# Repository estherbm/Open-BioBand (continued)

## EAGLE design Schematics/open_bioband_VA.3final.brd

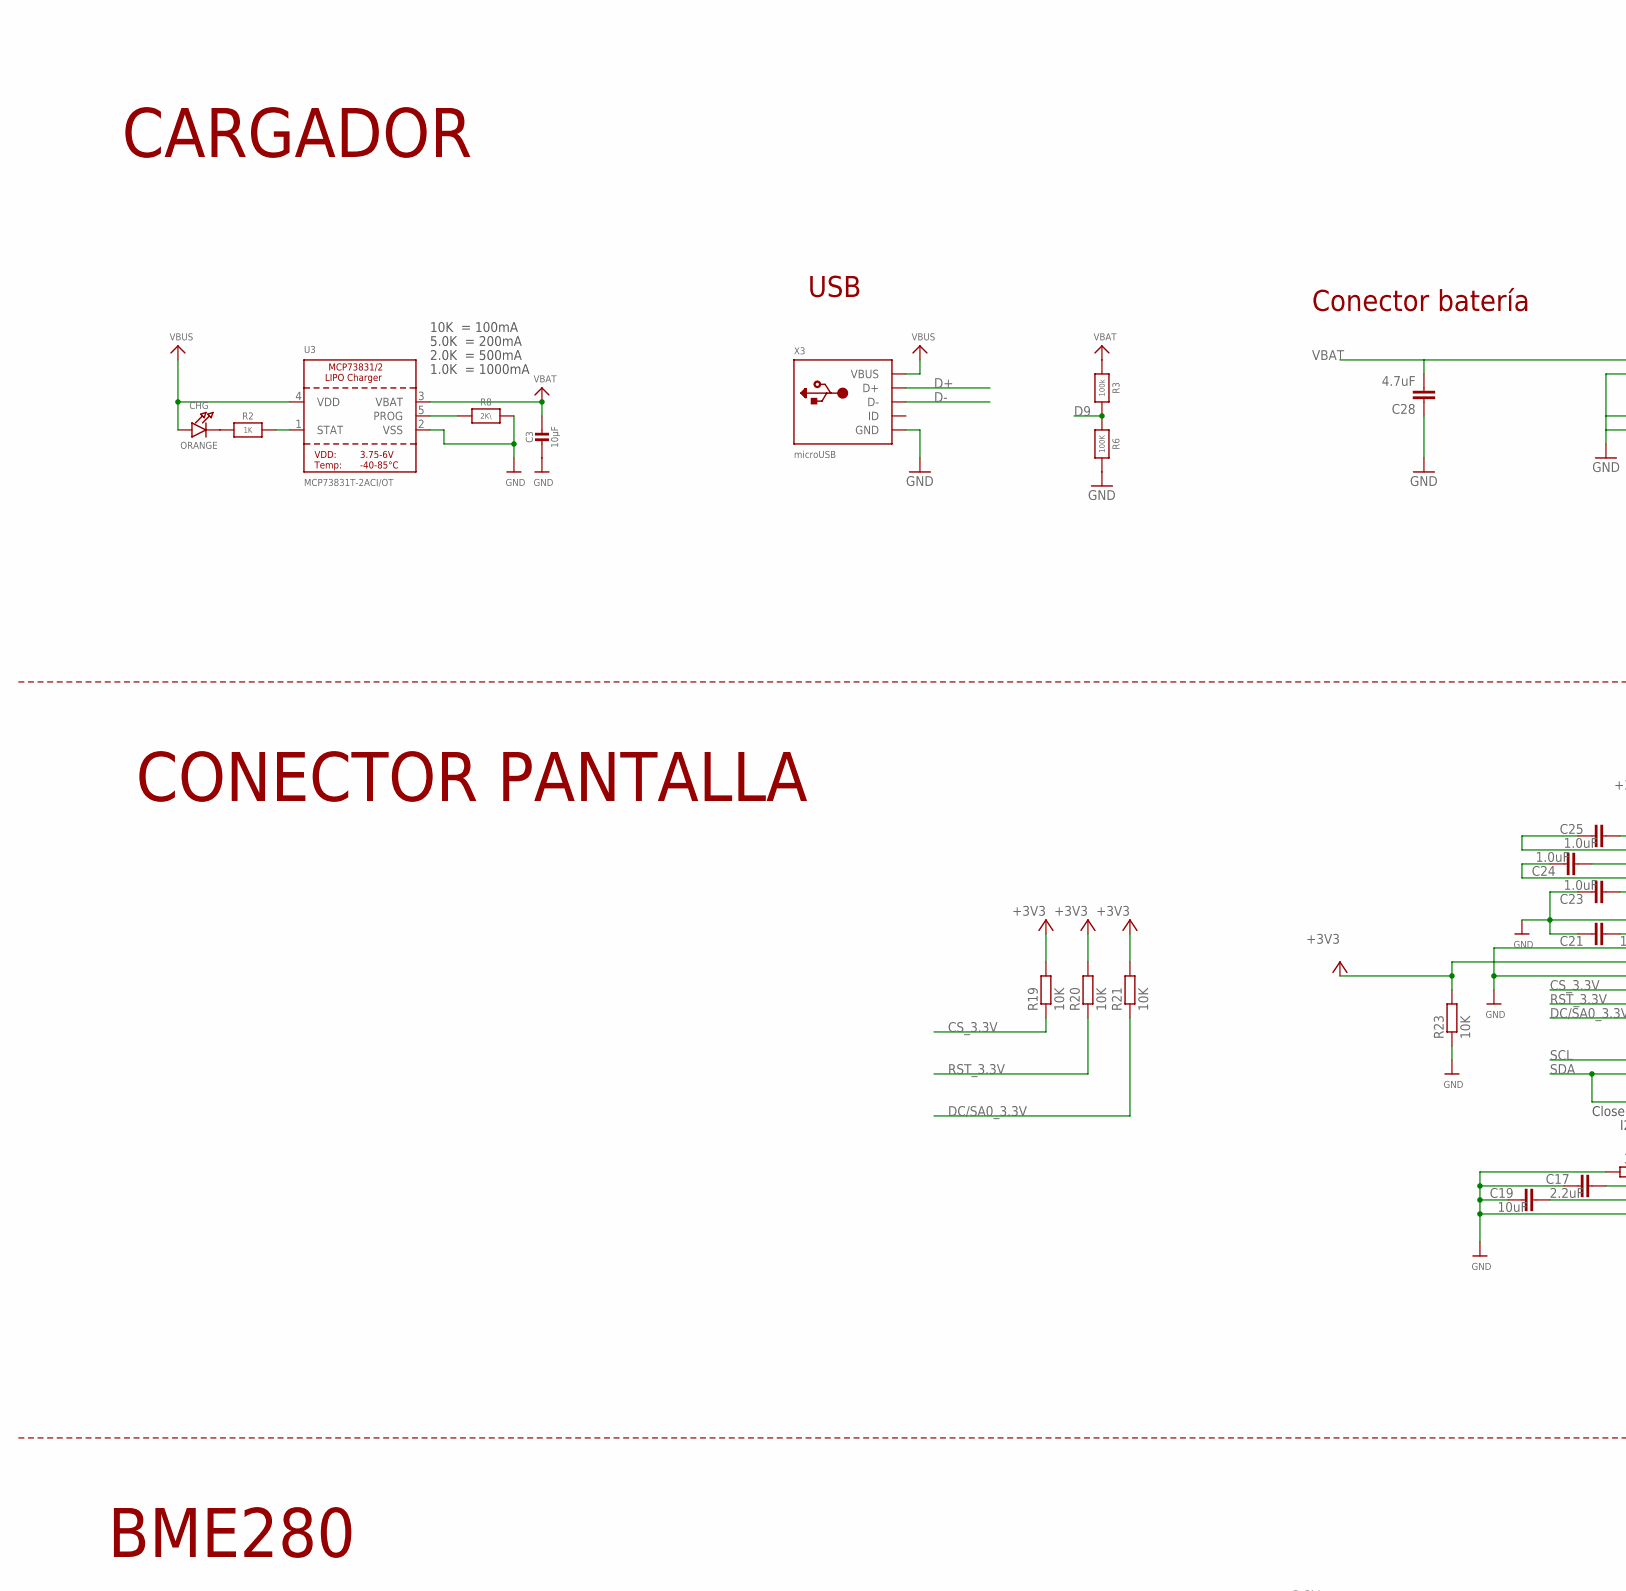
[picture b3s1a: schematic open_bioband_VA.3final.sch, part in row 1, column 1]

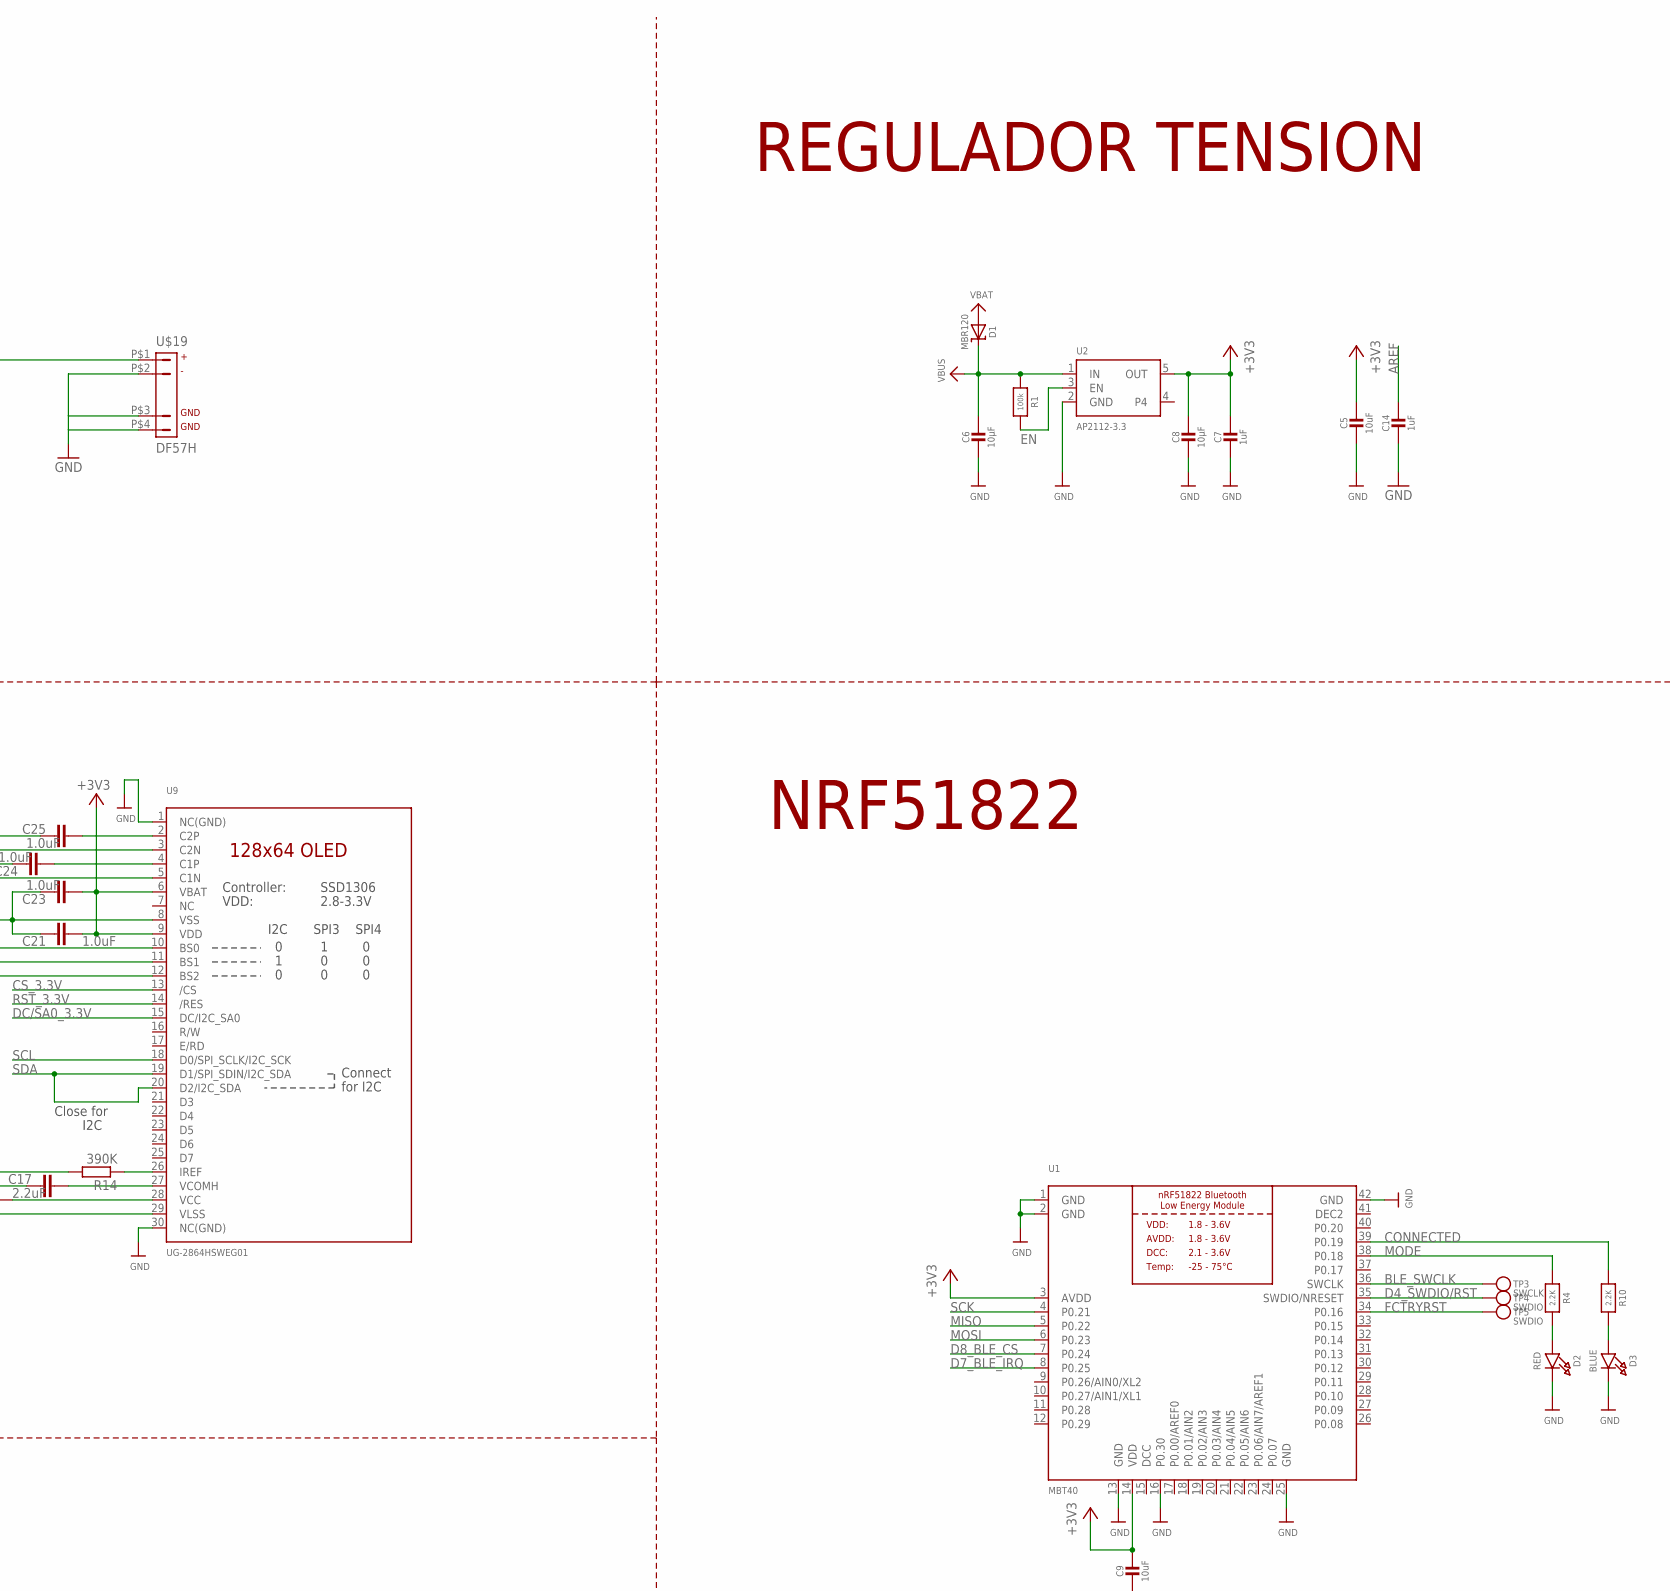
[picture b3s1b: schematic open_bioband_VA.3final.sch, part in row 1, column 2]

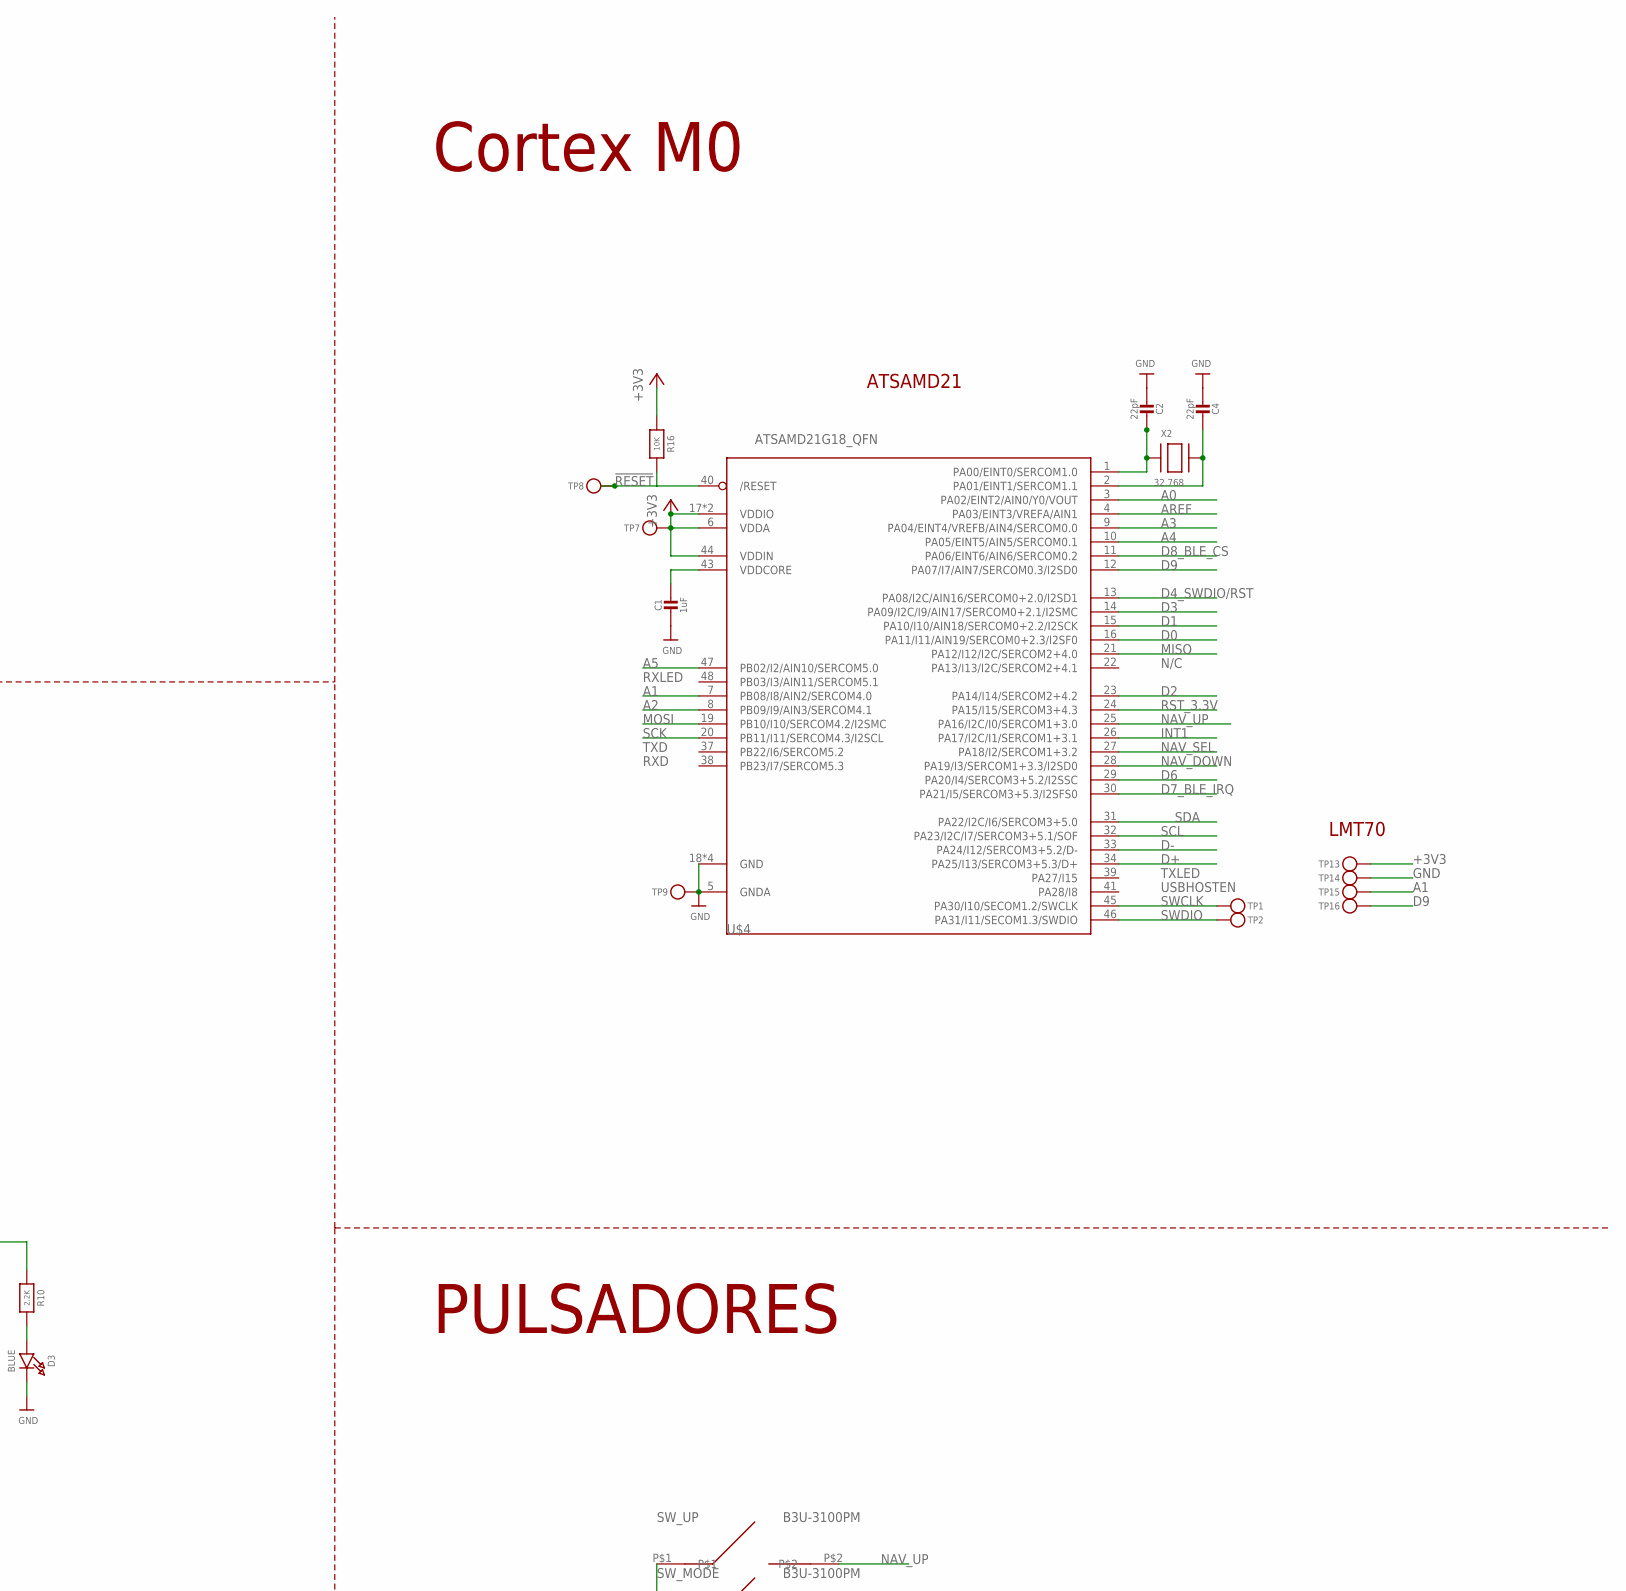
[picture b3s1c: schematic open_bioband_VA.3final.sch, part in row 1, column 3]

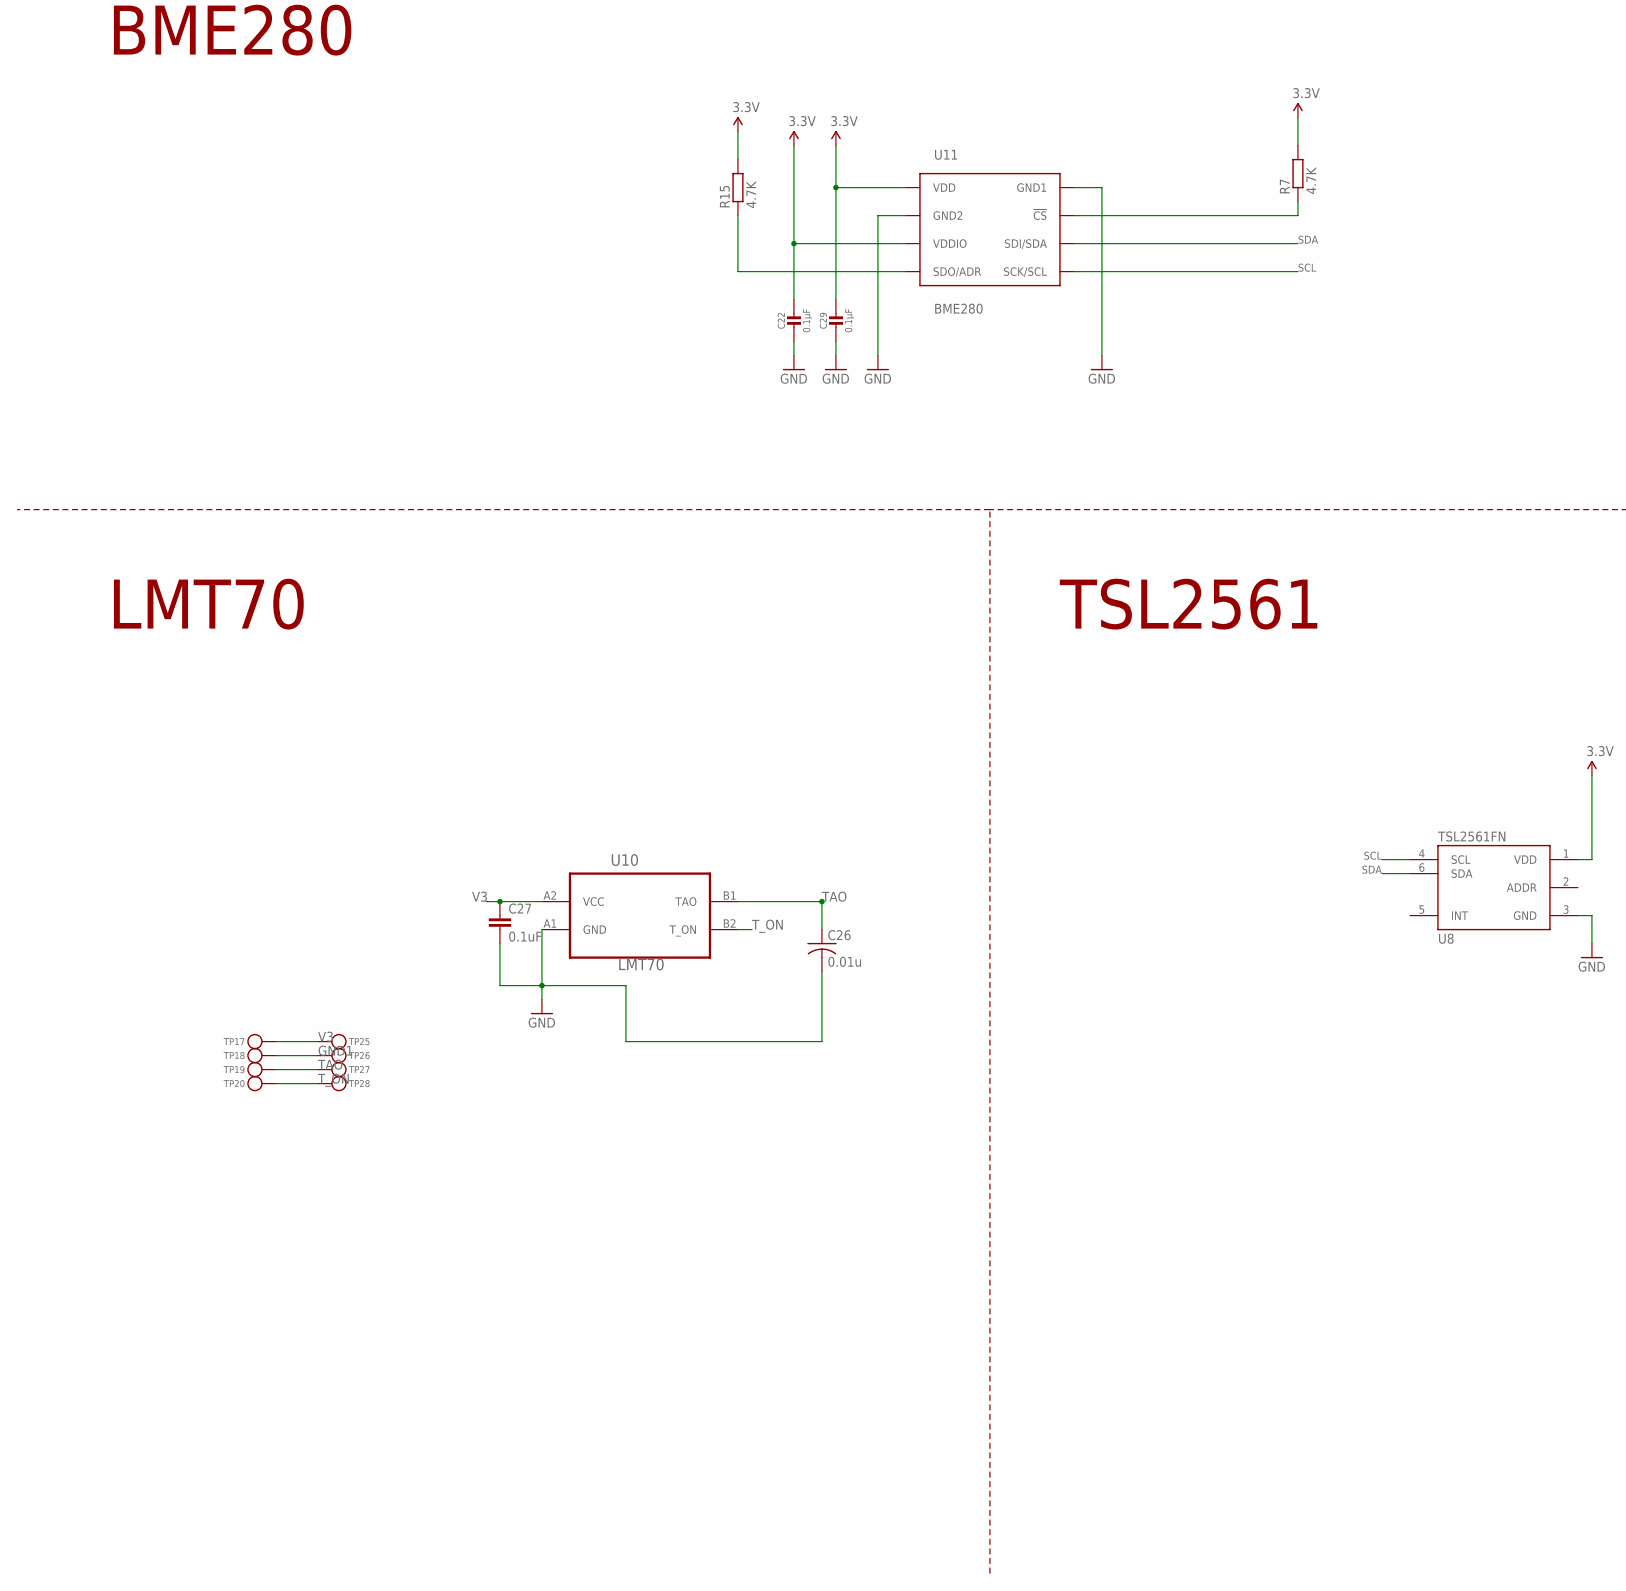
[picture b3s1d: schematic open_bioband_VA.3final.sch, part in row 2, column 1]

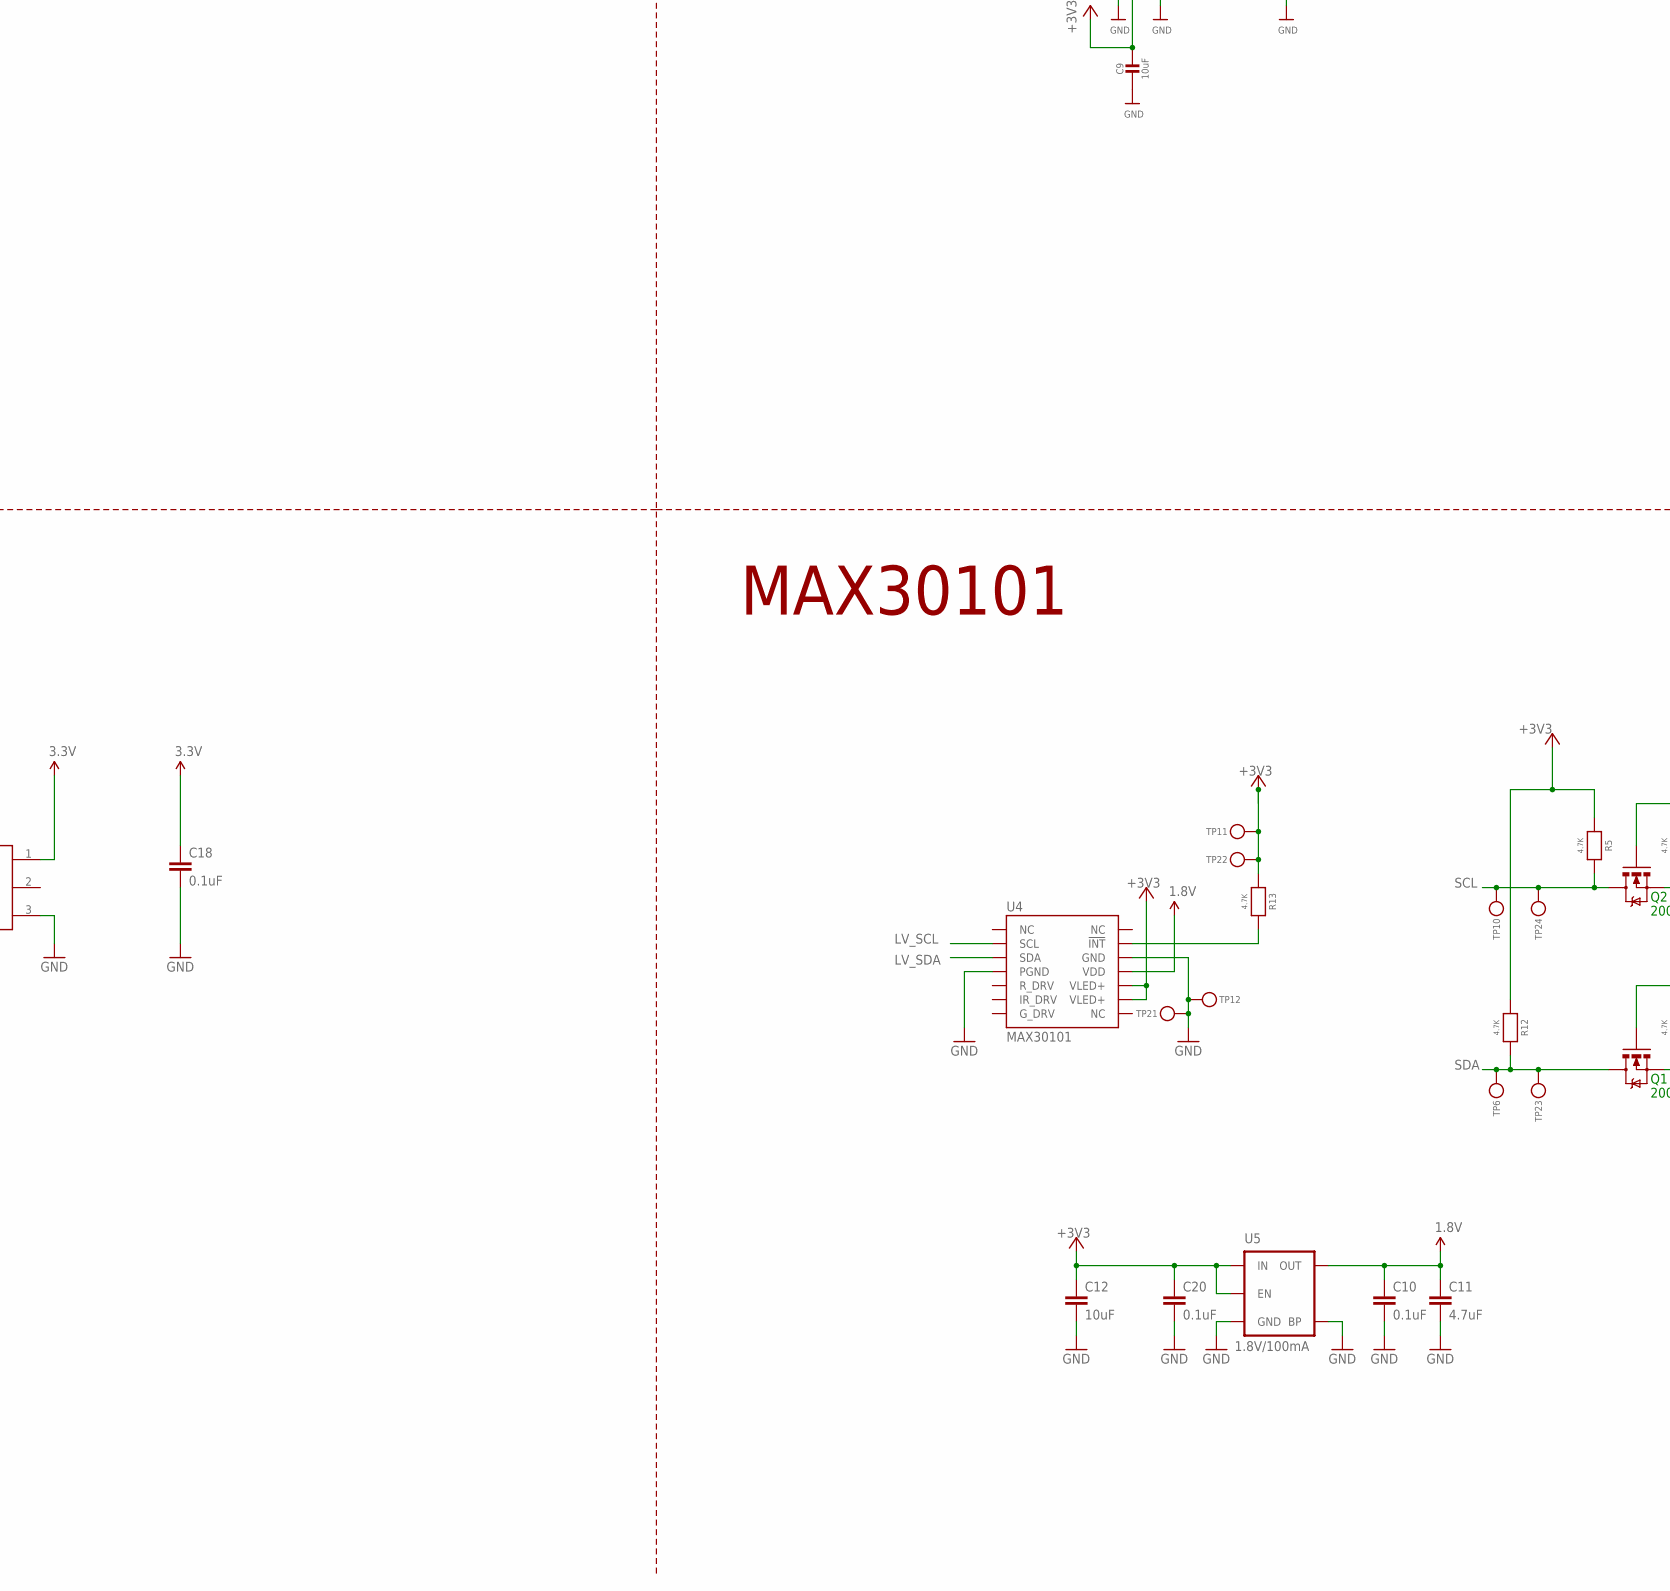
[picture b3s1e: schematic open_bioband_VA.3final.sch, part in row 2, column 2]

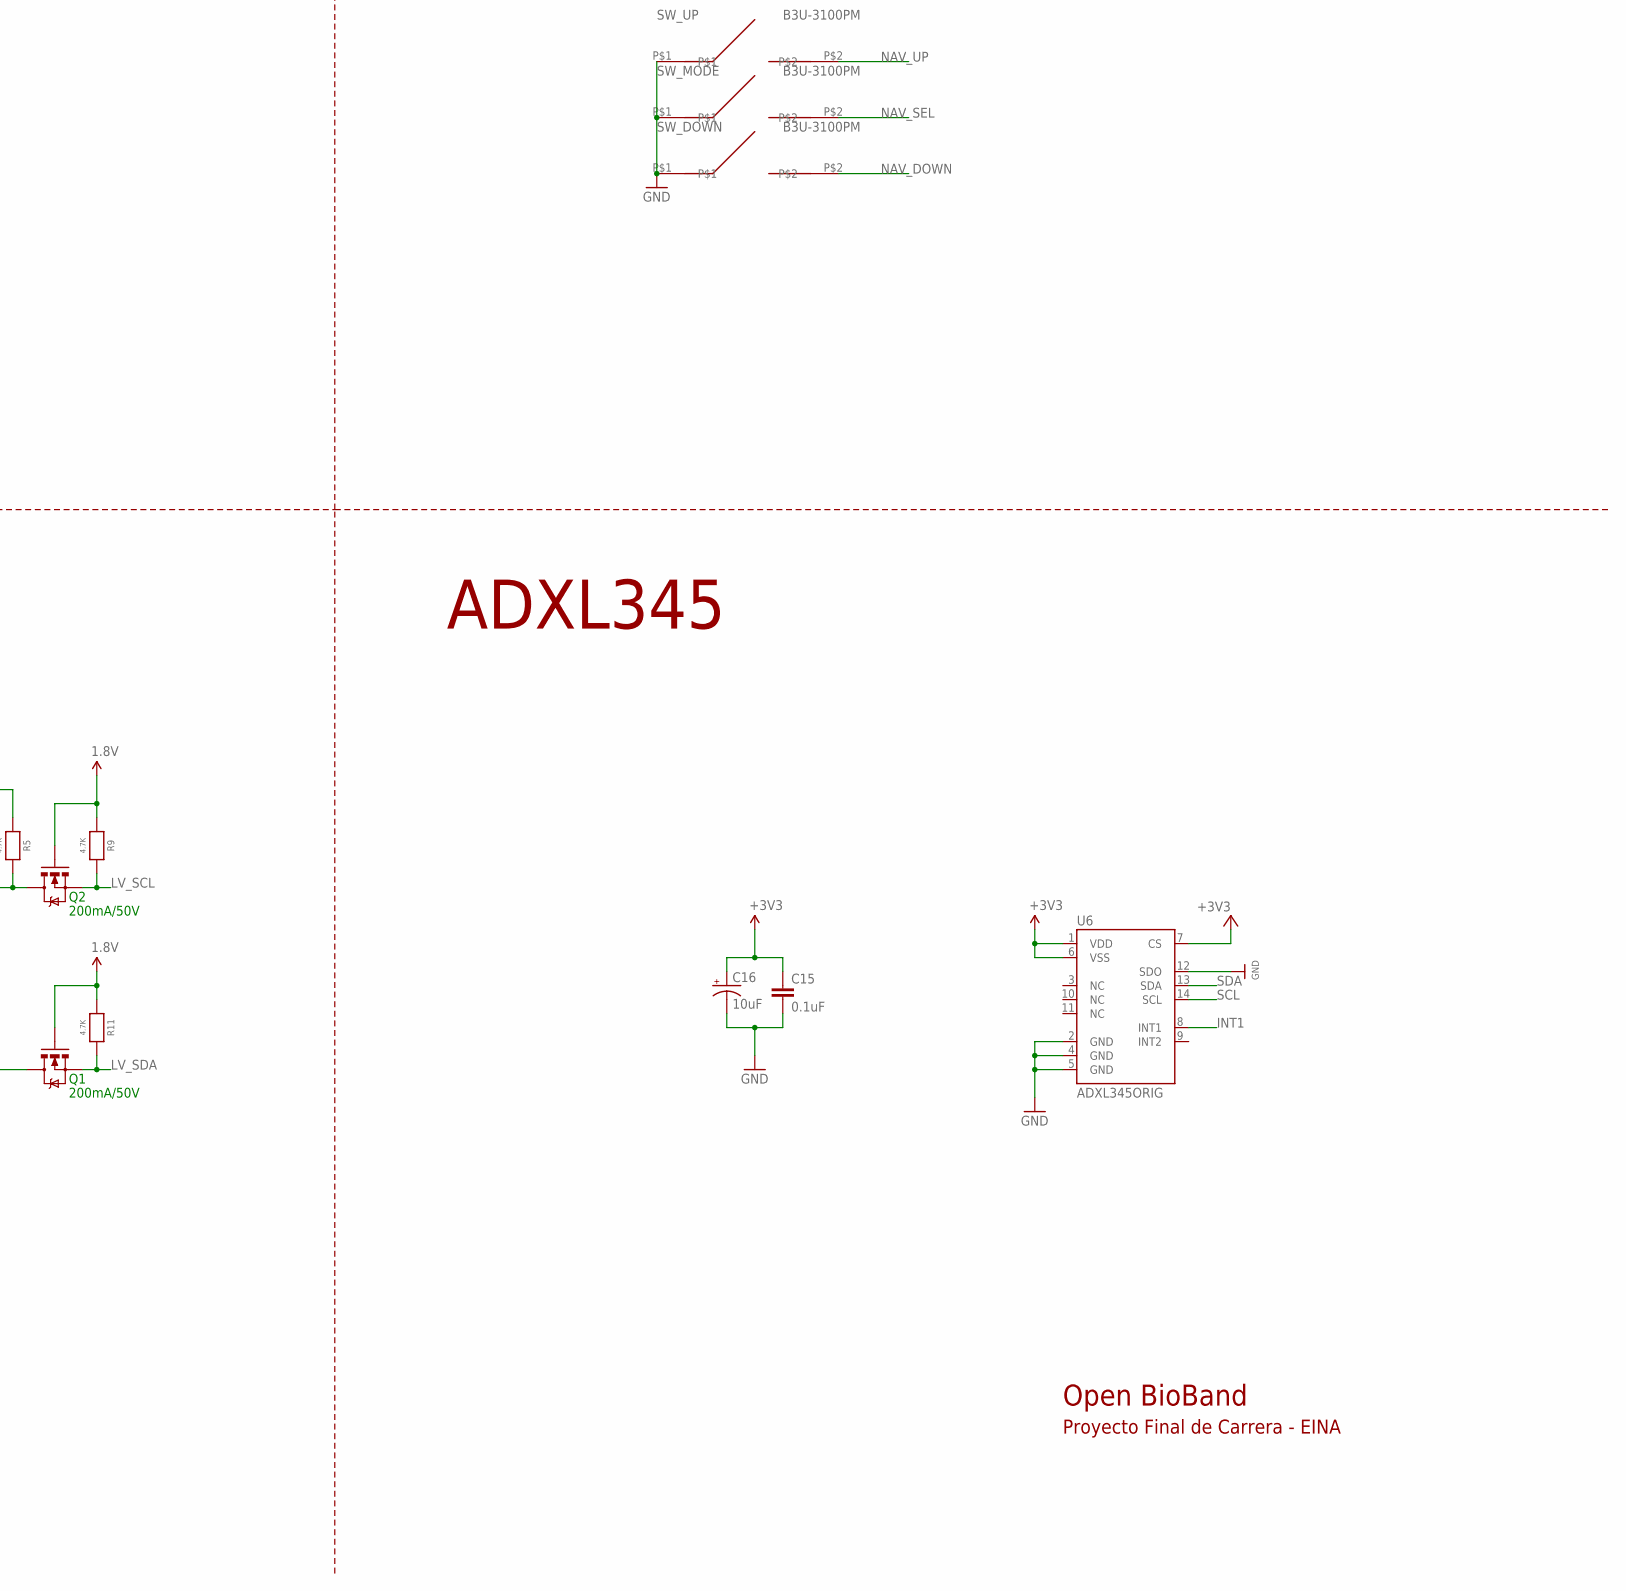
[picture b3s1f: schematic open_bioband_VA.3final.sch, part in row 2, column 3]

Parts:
C1, C7, C14: 1uF; _0402
C2, C4: 22pF; _0402
C3, C6, C8: 10µF; _0402
C5, C9: 10uF; _0402
C10, C15, C18, C20: 0.1uF; 0402-CAP
C11: 4.7uF; 0402-CAP
C12: 10uF; 0402-CAP
C16: 10uF; EIA3216
C17: 2.2uF; 0402
C19: 10uF; 0402
C21, C23, C24, C25: 1.0uF; 0402
C22, C29: 0.1µF; _0402
C26: 0.01u; C0402
C27: 0.1uF; 0402
C28: 4.7uF; C0402
CHG: ORANGE; CHIPLED_0603
D1: MBR120; SOD-123@1
D2: RED; CHIPLED_0603
D3: BLUE; CHIPLED_0603
Q1, Q2: 200mA/50V; SOT23-3
R1, R3: 100k; _0402
R2: 1K; _0402
R4, R10: 2.2K; _0402
R5, R9, R11, R12, R13: 4.7K; _0402
R6: 100K; _0402
R7, R15: 4.7K; R0402
R8: 2K\; _0402
R14: 390K; R0402
R16: 10K; _0402
R19, R20, R21, R23: 10K; R0402
SW_DOWN: B3U-3100PM
SW_MODE: B3U-3100PM
SW_UP: B3U-3100PM
TP1, TP2, TP7, TP8, TP9, TP13, TP14, TP15, TP16: TESTPOINTROUND1MM; TESTPOINT_ROUND_1MM
TP3: SWCLK; TESTPOINT_PAD_1MM
TP4, TP5: SWDIO; TESTPOINT_PAD_1MM
TP6, TP10, TP11, TP12: TESTPOINTROUND0.5MM; TESTPOINT_ROUND_0.5MM
TP17, TP18, TP19, TP20, TP21, TP22, TP23, TP24: TESTPOINT0.1"; 1X01_ROUND
TP25, TP26, TP27, TP28: TESTPOINTPAD2MM; TESTPOINT_PAD_2MM
U1: MBT40; BLE_MODULE_RAYTAC_MDBT40
U2: AP2112-3.3; SOT23-5
U3: MCP73831T-2ACI/OT; SOT23-5@1
U4: MAX30101; OLGA-14
U5: 1.8V/100mA; SC70
U6: ADXL345ORIG; LGA14
U8: TSL2561FN; FN-6
U9: UG-2864HSWEG01; UG-2864HSWEG01_0.96IN_WRAPAROUND
U10: LMT70LMT70; BGA4C40P2X2_77X77X50
U11: BME280; BME280_LGA
U$4: ATSAMD21G18_QFN; TQFN48_7MM
U$19: DF57H; DF57H-2P
X2: 32.768; XTAL3215
X3: microUSB; 4UCONN_20329_V2

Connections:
1.8V: C10.1, C11.1, Q1.1 (G), Q2.1 (G), R9.1, R11.1, U4.11 (VDD), U5.5 (OUT)
!CS1: R7.1, U11.P$2 (!CS)
!INT: R13.2, U4.13 (!INT)
!RESET: R16.2, TP8.P$1, U$4.40 (/RESET)
+3V3: C5.1, C7.1, C8.1, C9.1, C12.1, C15.1, C16.A (+), C18.1, C20.1, C21.2, C22.1, C23.2, C29.1, R5.1, R7.2, R12.1, R13.1, R15.2, R16.1, R19.2, R20.2, R21.2, R23.2, TP7.P$1, TP11.P$1, TP13.P$1, TP22.1, U1.3 (AVDD), U1.14 (VDD), U2.5 (OUT), U4.9 (VLED+), U4.10 (VLED+), U5.1 (IN), U5.3 (EN), U6.1 (VDD), U6.6 (VSS), U6.7 (CS), U8.1 (VDD), U9.6 (VBAT), U9.9 (VDD), U9.11 (BS1), U11.P$6 (VDDIO), U11.P$8 (VDD), U$4.6 (VDDA), U$4.17 (VDDIO), U$4.36 (VDDIO), U$4.44 (VDDIN)
A0: U$4.3 (PA02/EINT2/AIN0/Y0/VOUT)
A1: TP15.P$1, U$4.7 (PB08/I8/AIN2/SERCOM4.0)
A2: U$4.8 (PB09/I9/AIN3/SERCOM4.1)
A3: U$4.9 (PA04/EINT4/VREFB/AIN4/SERCOM0.0)
A4: U$4.10 (PA05/EINT5/AIN5/SERCOM0.1)
A5: U$4.47 (PB02/I2/AIN10/SERCOM5.0)
AREF: C14.1, U$4.4 (PA03/EINT3/VREFA/AIN1)
BLE_SWCLK: TP3.P$1, U1.36 (SWCLK)
CONNECTED: R10.1, U1.39 (P0.19)
CS_3.3V: R19.1, U9.13 (/CS)
D0: U$4.16 (PA11/I11/AIN19/SERCOM0+2.3/I2SF0)
D1: U$4.15 (PA10/I10/AIN18/SERCOM0+2.2/I2SCK)
D2: U$4.23 (PA14/I14/SERCOM2+4.2)
D3: U$4.14 (PA09/I2C/I9/AIN17/SERCOM0+2.1/I2SMC)
D4_SWDIO/RST: TP4.P$1, U1.35 (SWDIO/NRESET), U$4.13 (PA08/I2C/AIN16/SERCOM0+2.0/I2SD1)
D6: U$4.29 (PA20/I4/SERCOM3+5.2/I2SSC)
D7_BLE_IRQ: U1.8 (P0.25), U$4.30 (PA21/I5/SERCOM3+5.3/I2SFS0)
D8_BLE_CS: U1.7 (P0.24), U$4.11 (PA06/EINT6/AIN6/SERCOM0.2)
D9: R3.2, R6.1, TP16.P$1, U$4.12 (PA07/I7/AIN7/SERCOM0.3/I2SD0)
D+: U$4.34 (PA25/I13/SERCOM3+5.3/D+), X3.D+
D-: U$4.33 (PA24/I12/SERCOM3+5.2/D-), X3.D-
DC/SA0_3.3V: R21.1, U9.15 (DC/I2C_SA0)
DCC: U1.15 (DCC)
DEC2: U1.41 (DEC2)
EN: R1.2, U2.3 (EN)
FCTRYRST: TP5.P$1, U1.34 (P0.16)
GND: C1.2, C2.2, C3.2, C4.2, C5.2, C6.2, C7.2, C8.2, C9.2, C10.2, C11.2, C12.2, C14.2, C15.2, C16.C (-), C17.1, C18.2, C19.1, C20.2, C21.1, C22.2, C23.1, C28.1, C29.2, D2.C, D3.C, R6.2, R8.2, R14.2, R23.1, SW_DOWN.P$1, SW_MODE.P$1, SW_UP.P$1, TP9.P$1, TP12.P$1, TP14.P$1, TP21.1, U1.1 (GND), U1.2 (GND), U1.13 (GND), U1.16 (P0.30), U1.25 (GND), U1.42 (GND), U2.2 (GND), U3.2 (VSS), U4.4 (PGND), U4.12 (GND), U5.2 (GND), U5.4 (BP), U6.2 (GND), U6.4 (GND), U6.5 (GND), U6.12 (SDO), U8.3 (GND), U9.1 (NC(GND)), U9.8 (VSS), U9.10 (BS0), U9.12 (BS2), U9.29 (VLSS), U9.30 (NC(GND)), U11.P$1 (GND1), U11.P$7 (GND2), U$4.5 (GNDA), U$4.18 (GND), U$4.35 (GND), U$4.42 (GND), U$4.THERMAL (GND), U$19.P$2 (2), U$19.P$3 (5), U$19.P$4 (6), X3.BASE@1 (GND), X3.BASE@2 (GND), X3.GND, X3.SPRT@1 (GND), X3.SPRT@2 (GND), X3.SPRT@3 (GND), X3.SPRT@4 (GND)
GND1: C26.2, C27.2, TP18.1, TP26.P$1, U10.A1 (GND)
INT1: U6.8 (INT1), U$4.26 (PA17/I2C/I1/SERCOM1+3.1)
LV_SCL: Q2.2 (S), R9.2, U4.2 (SCL)
LV_SDA: Q1.2 (S), R11.2, U4.3 (SDA)
MISO: U1.5 (P0.22), U$4.21 (PA12/I12/I2C/SERCOM2+4.0)
MODE: R4.1, U1.38 (P0.18)
MOSI: U1.6 (P0.23), U$4.19 (PB10/I10/SERCOM4.2/I2SMC)
unnamed: CHG.C, R2.1
unnamed: R2.2, U3.1 (STAT)
unnamed: R8.1, U3.5 (PROG)
unnamed: C2.1, U$4.1 (PA00/EINT0/SERCOM1.0), X2.P$1
unnamed: D2.A, R4.2
unnamed: C4.1, U$4.2 (PA01/EINT1/SERCOM1.1), X2.P$2
unnamed: D3.A, R10.2
unnamed: R14.1, U9.26 (IREF)
unnamed: C25.2, U9.2 (C2P)
unnamed: C25.1, U9.3 (C2N)
unnamed: C24.2, U9.4 (C1P)
unnamed: C24.1, U9.5 (C1N)
unnamed: C19.2, U9.28 (VCC)
unnamed: C17.2, U9.27 (VCOMH)
NAV_DOWN: SW_DOWN.P$2, U$4.28 (PA19/I3/SERCOM1+3.3/I2SD0)
NAV_SEL: SW_MODE.P$2, U$4.27 (PA18/I2/SERCOM1+3.2)
NAV_UP: SW_UP.P$2, U$4.25 (PA16/I2C/I0/SERCOM1+3.0)
RST_3.3V: R20.1, U9.14 (/RES), U$4.24 (PA15/I15/SERCOM3+4.3)
SCK: U1.4 (P0.21), U$4.20 (PB11/I11/SERCOM4.3/I2SCL)
SCL: Q2.3 (D), R5.2, TP10.P$1, TP24.1, U6.14 (SCL), U8.4 (SCL), U9.18 (D0/SPI_SCLK/I2C_SCK), U11.P$4 (SCK/SCL), U$4.32 (PA23/I2C/I7/SERCOM3+5.1/SOF)
SDA: Q1.3 (D), R12.2, TP6.P$1, TP23.1, U6.13 (SDA), U8.6 (SDA), U9.19 (D1/SPI_SDIN/I2C_SDA), U9.20 (D2/I2C_SDA), U11.P$3 (SDI/SDA), U$4.31 (PA22/I2C/I6/SERCOM3+5.0)
SDO/ADR1: R15.1, U11.P$5 (SDO/ADR)
SWCLK: TP1.P$1, U$4.45 (PA30/I10/SECOM1.2/SWCLK)
SWDIO: TP2.P$1, U$4.46 (PA31/I11/SECOM1.3/SWDIO)
TAO: C26.1, TP19.1, TP27.P$1, U10.B1 (TAO)
T_ON: TP20.1, TP28.P$1, U10.B2 (T_ON)
V3: C27.1, TP17.1, TP25.P$1, U10.A2 (VCC)
VBAT: C3.1, C28.2, D1.A, R3.1, U3.3 (VBAT), U$19.P$1 (1)
VBUS: C6.1, CHG.A, D1.C, R1.1, U2.1 (IN), U3.4 (VDD), X3.VBUS
VDDCORE: C1.1, U$4.43 (VDDCORE)

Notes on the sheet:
10K = 100mA
5.0K = 200mA
2.0K = 500mA
1.0K = 1000mA
N/C
TXLED
USBHOSTEN
RXLED
TXD
RXD
ATSAMD21
Close for
I2C
LMT70
Conector batería
Open BioBand
Proyecto Final de Carrera - EINA
Cortex M0
CARGADOR
REGULADOR TENSION
CONECTOR PANTALLA
NRF51822
BME280
TSL2561
ADXL345
MAX30101
PULSADORES
USB

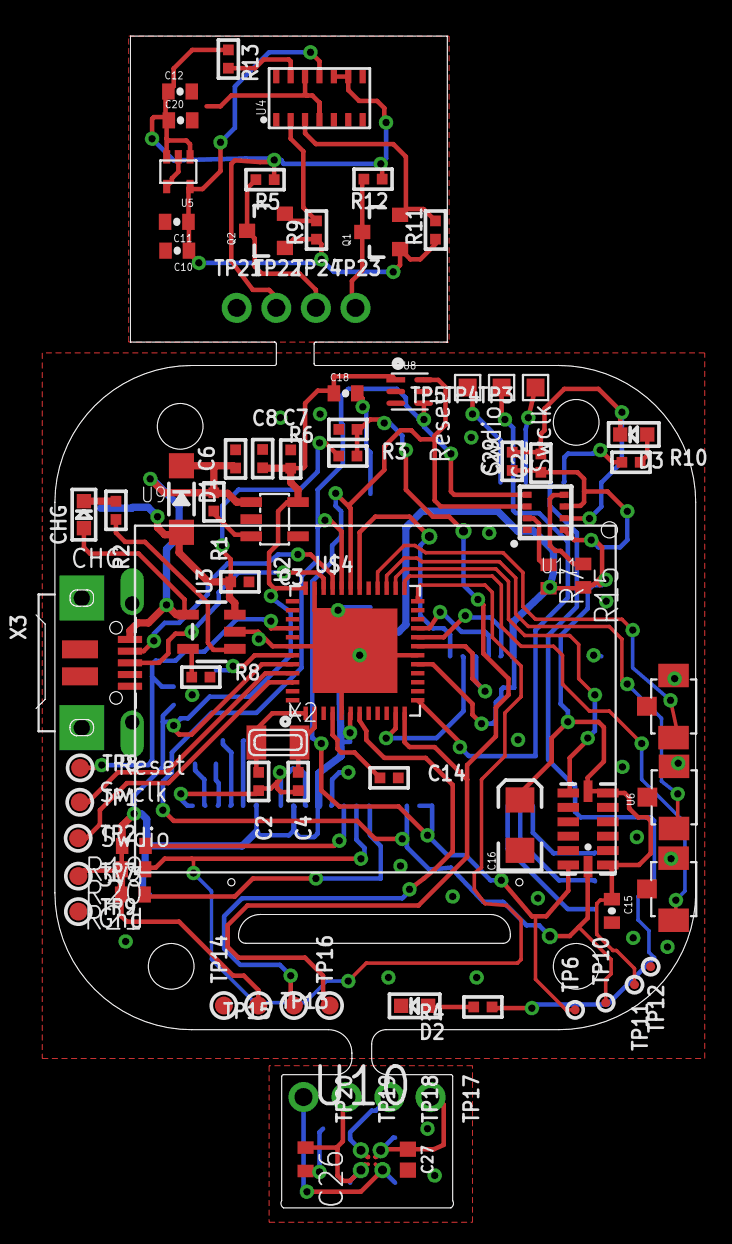
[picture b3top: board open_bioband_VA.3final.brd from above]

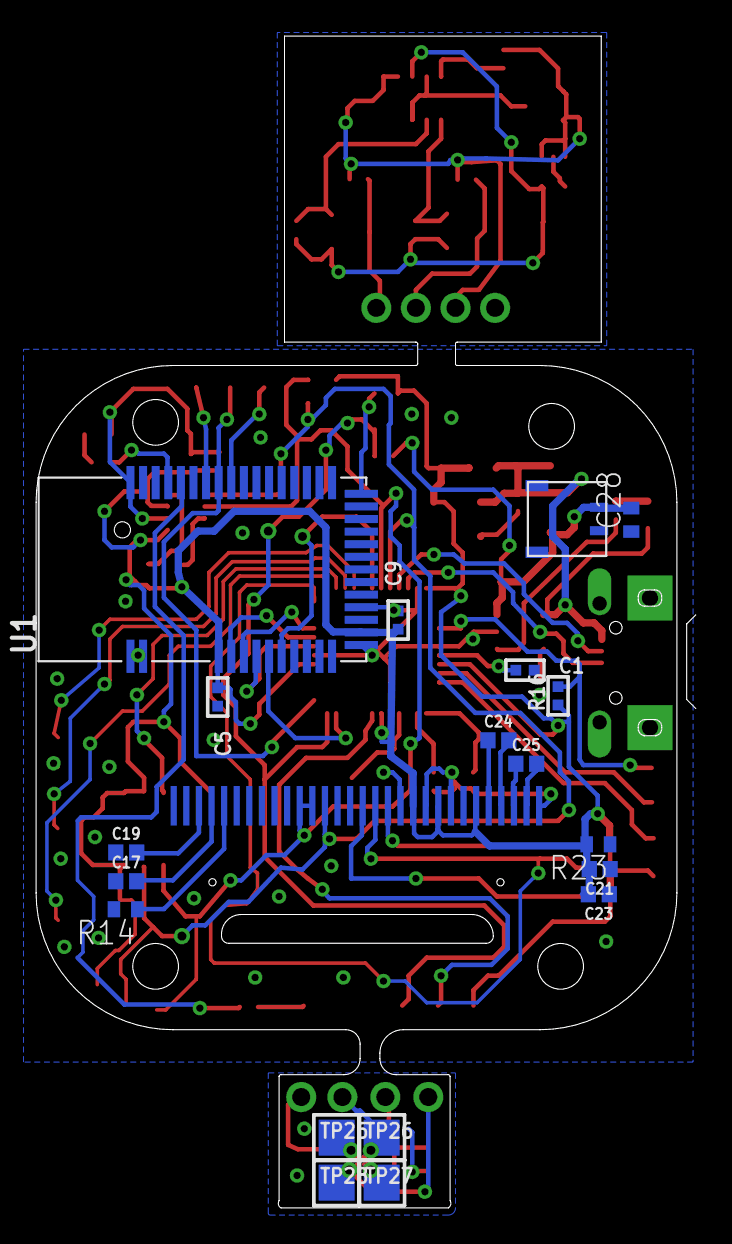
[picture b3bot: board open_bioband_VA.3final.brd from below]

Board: 2 copper layers, 36.6 x 65.1 mm, 99 parts (19 on the bottom side), 57 nets.

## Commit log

2017-10-10 Subiendo a Github
2017-10-10 Subiendo a Github2
2017-10-10 Updating files
2017-10-11 Removed folder from repository
